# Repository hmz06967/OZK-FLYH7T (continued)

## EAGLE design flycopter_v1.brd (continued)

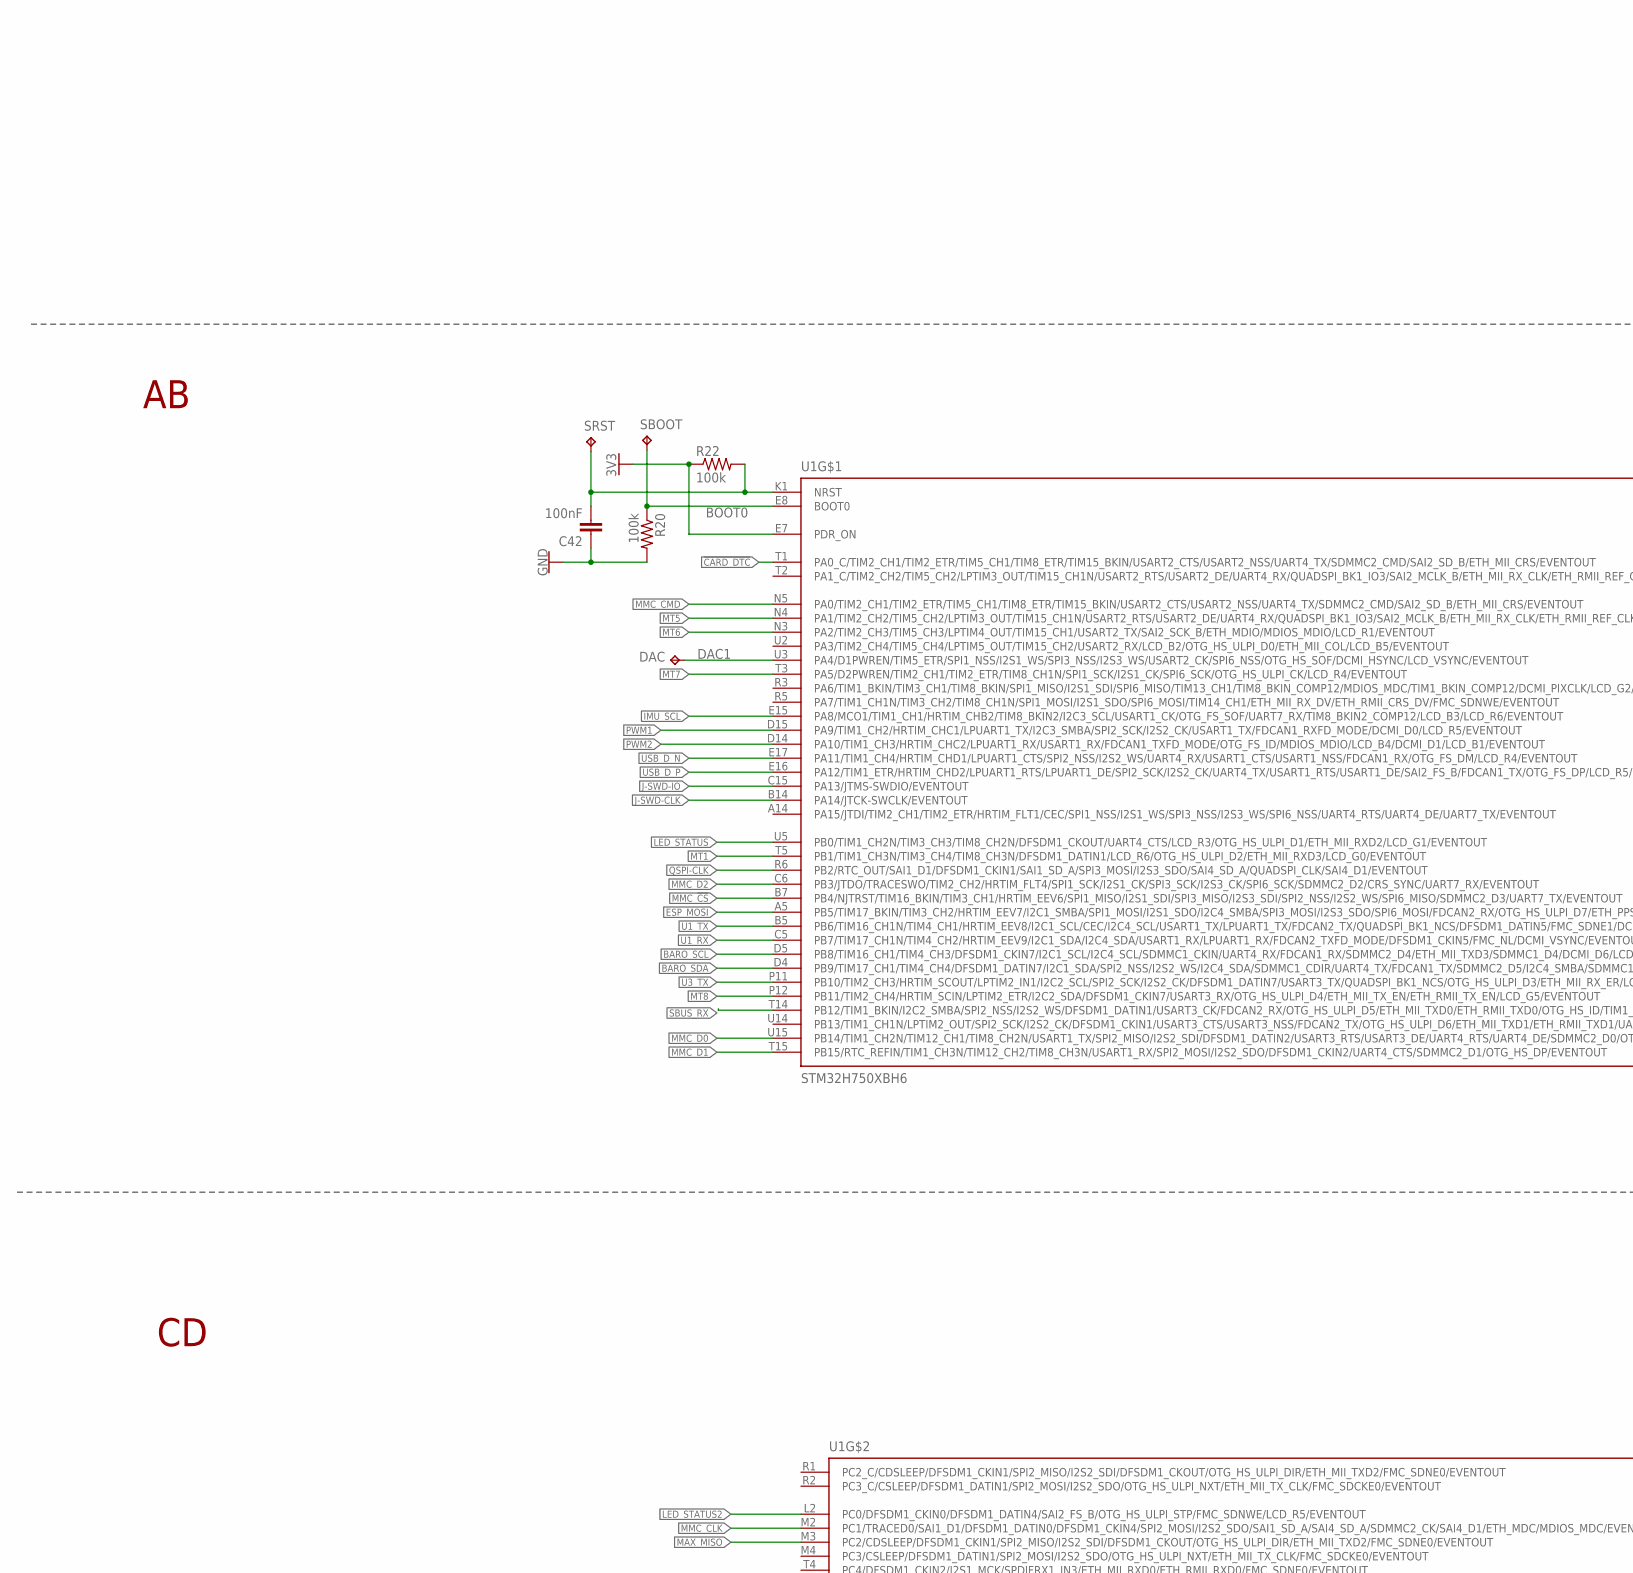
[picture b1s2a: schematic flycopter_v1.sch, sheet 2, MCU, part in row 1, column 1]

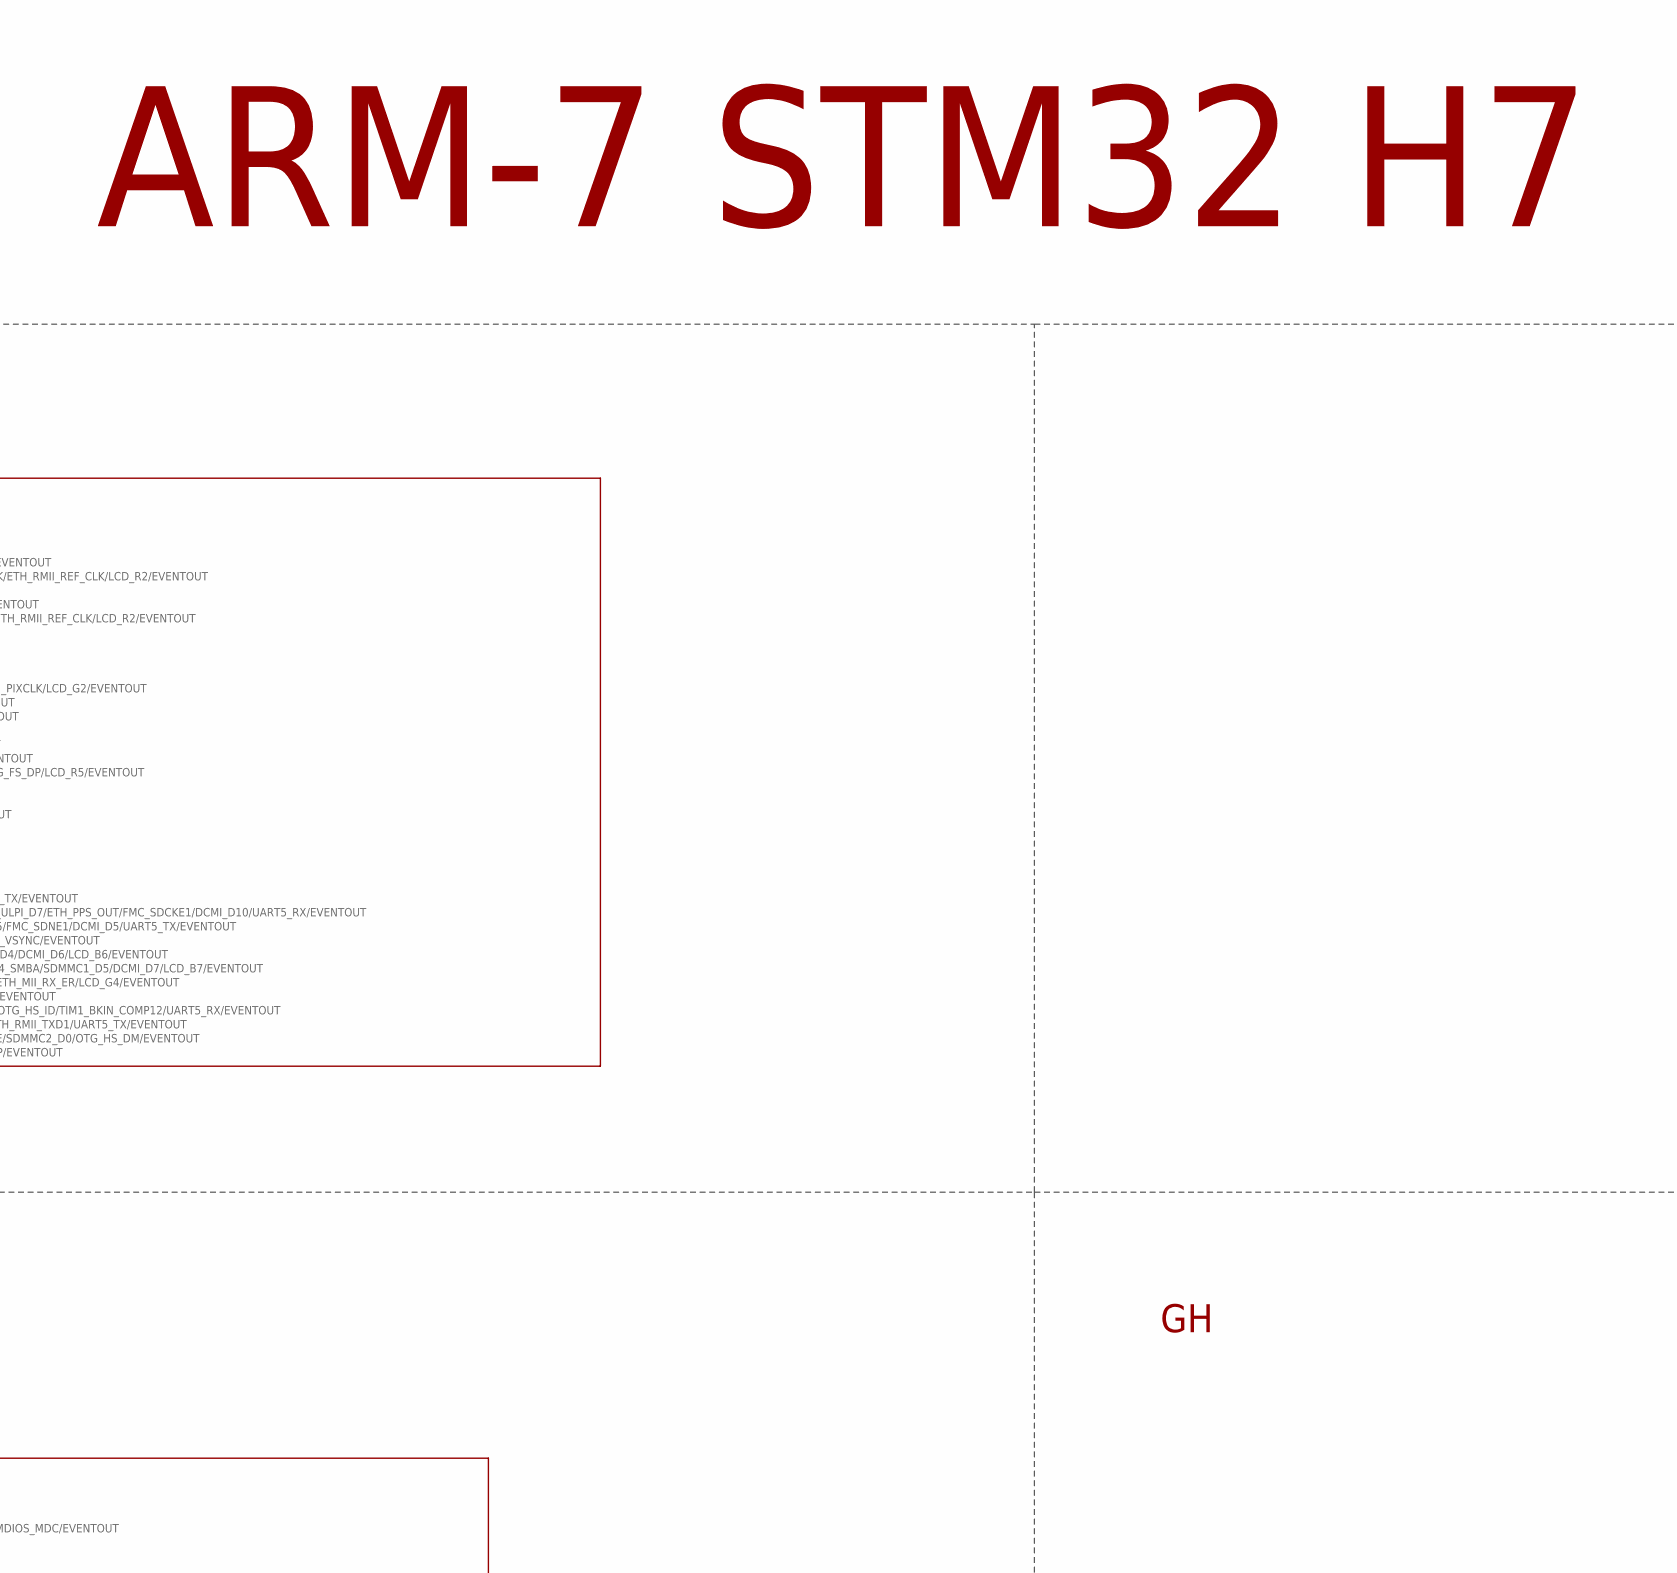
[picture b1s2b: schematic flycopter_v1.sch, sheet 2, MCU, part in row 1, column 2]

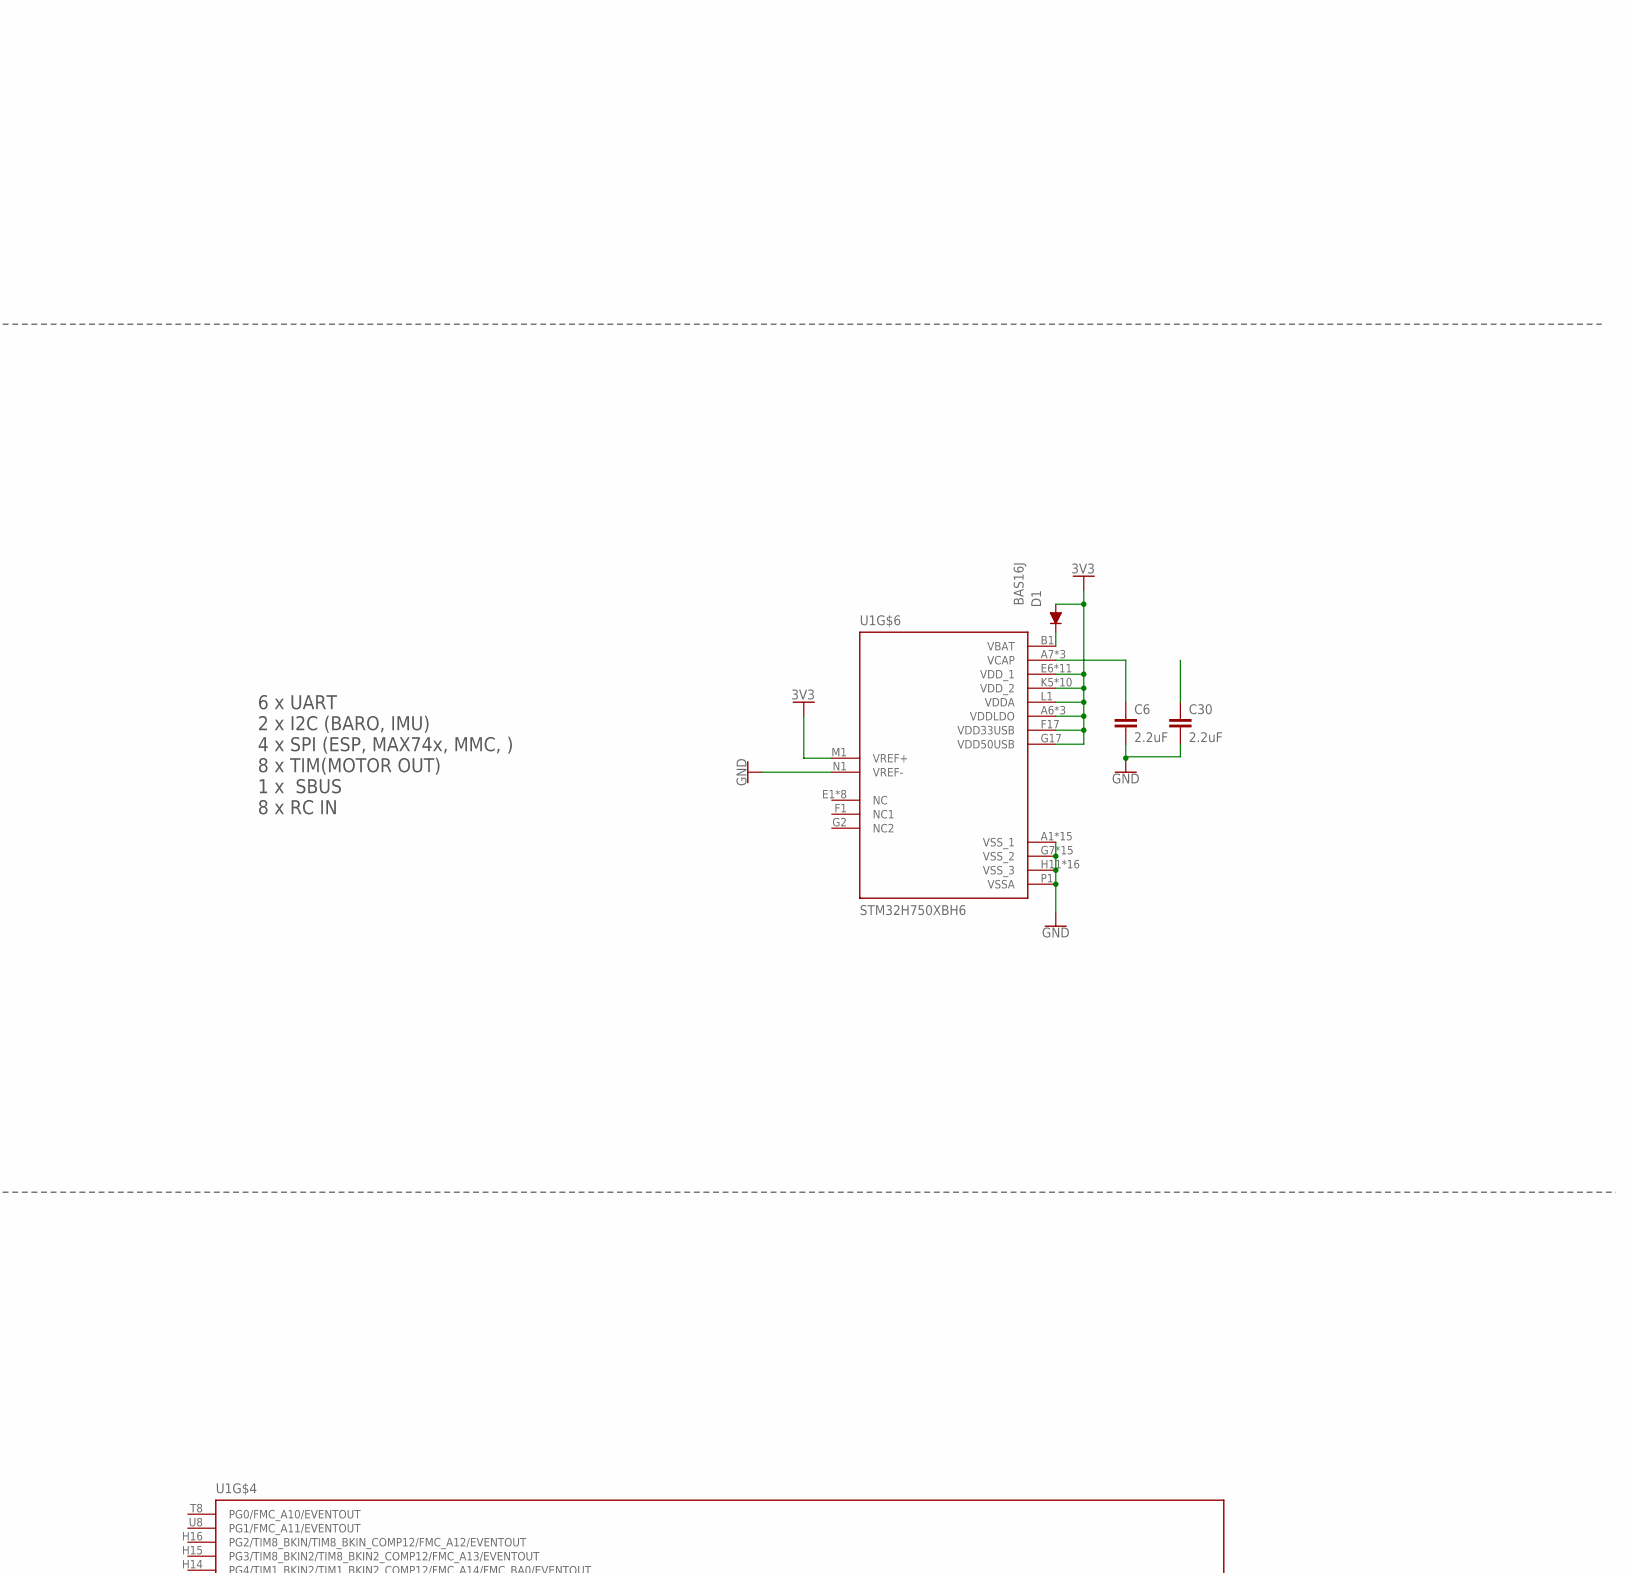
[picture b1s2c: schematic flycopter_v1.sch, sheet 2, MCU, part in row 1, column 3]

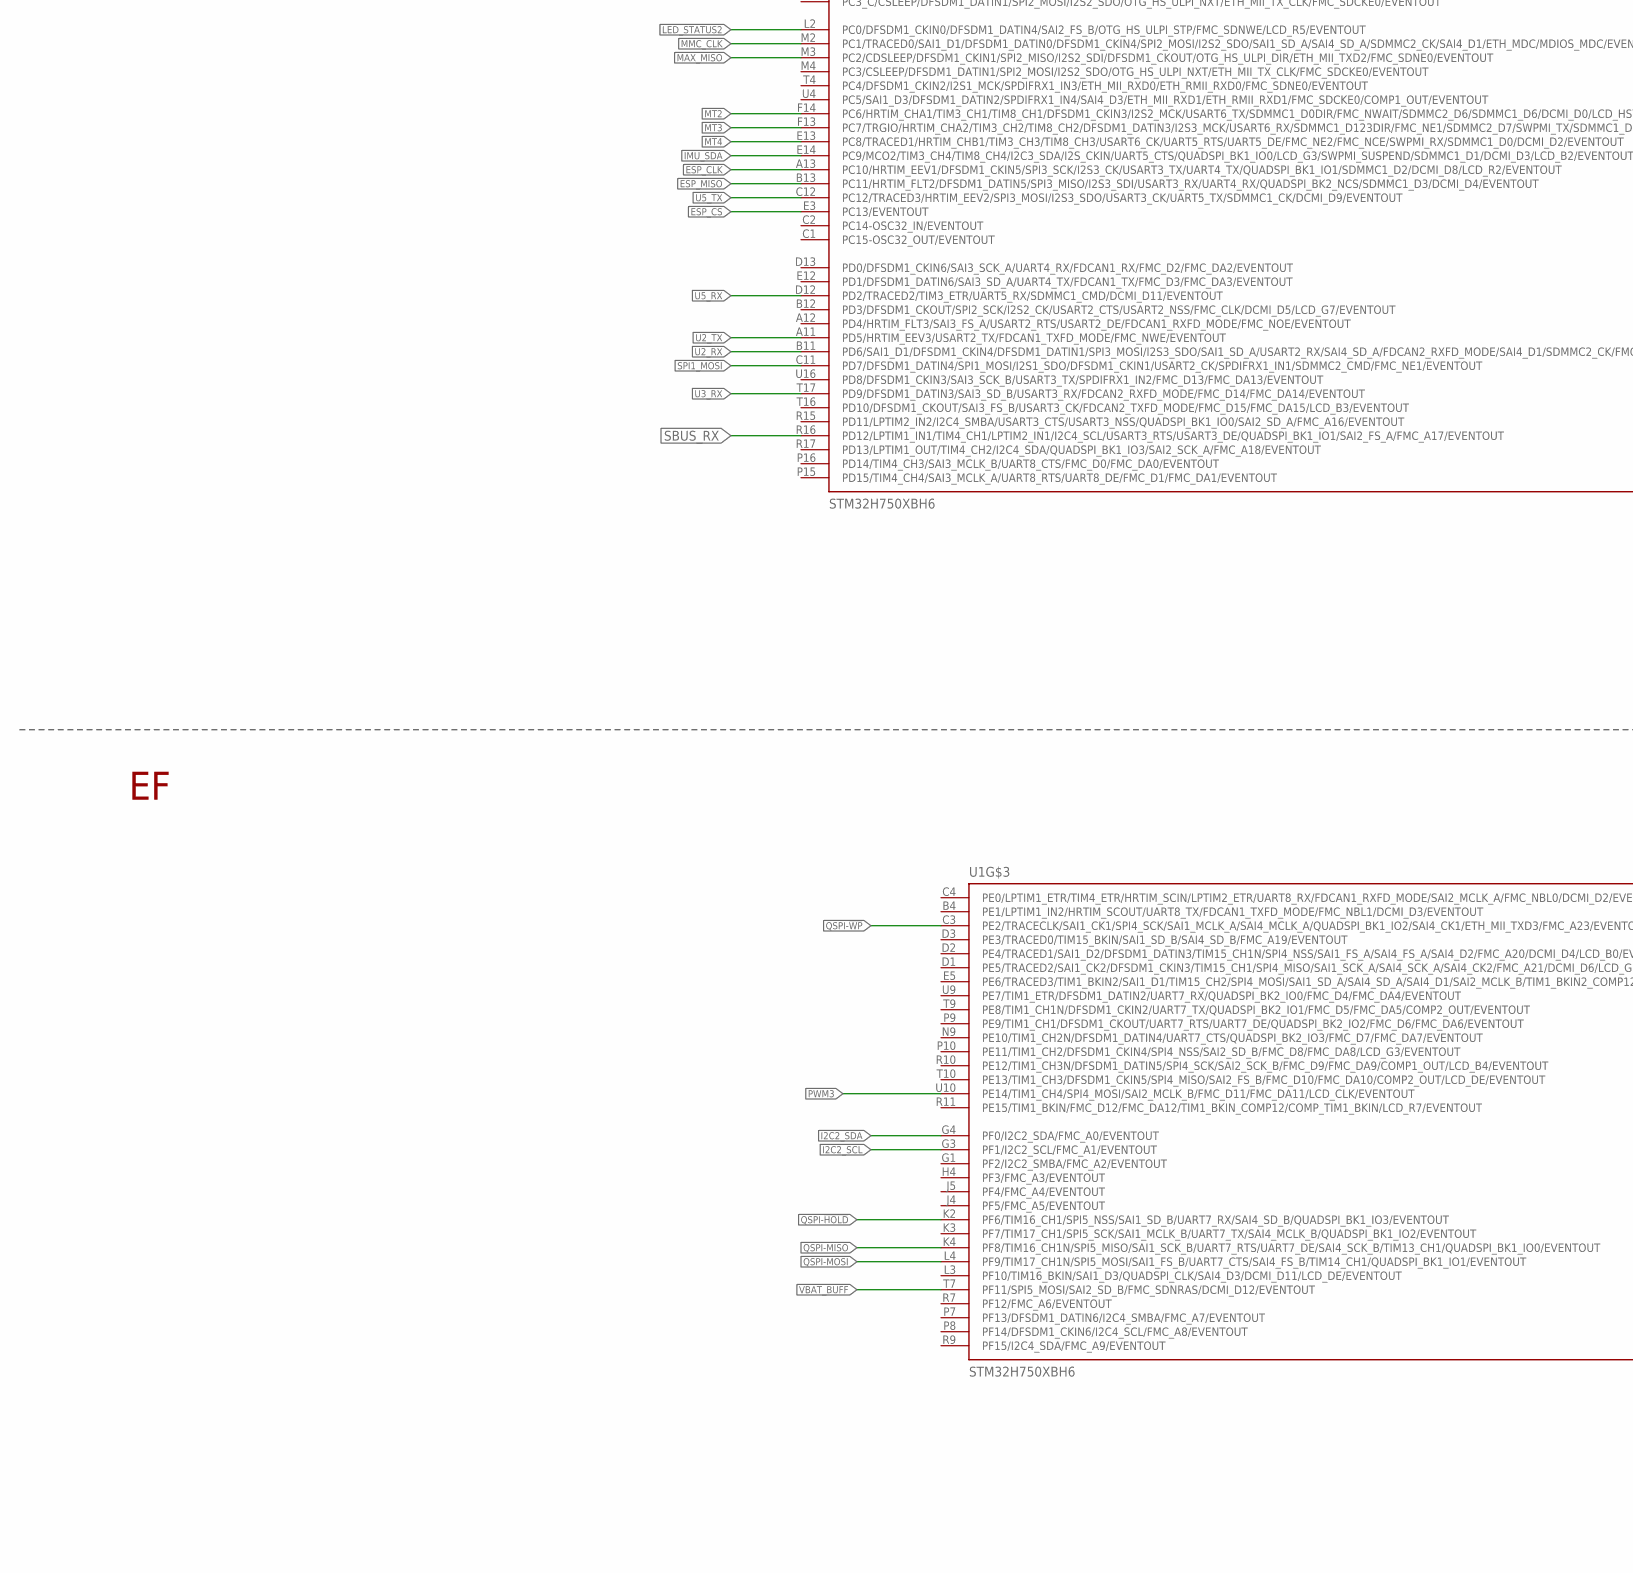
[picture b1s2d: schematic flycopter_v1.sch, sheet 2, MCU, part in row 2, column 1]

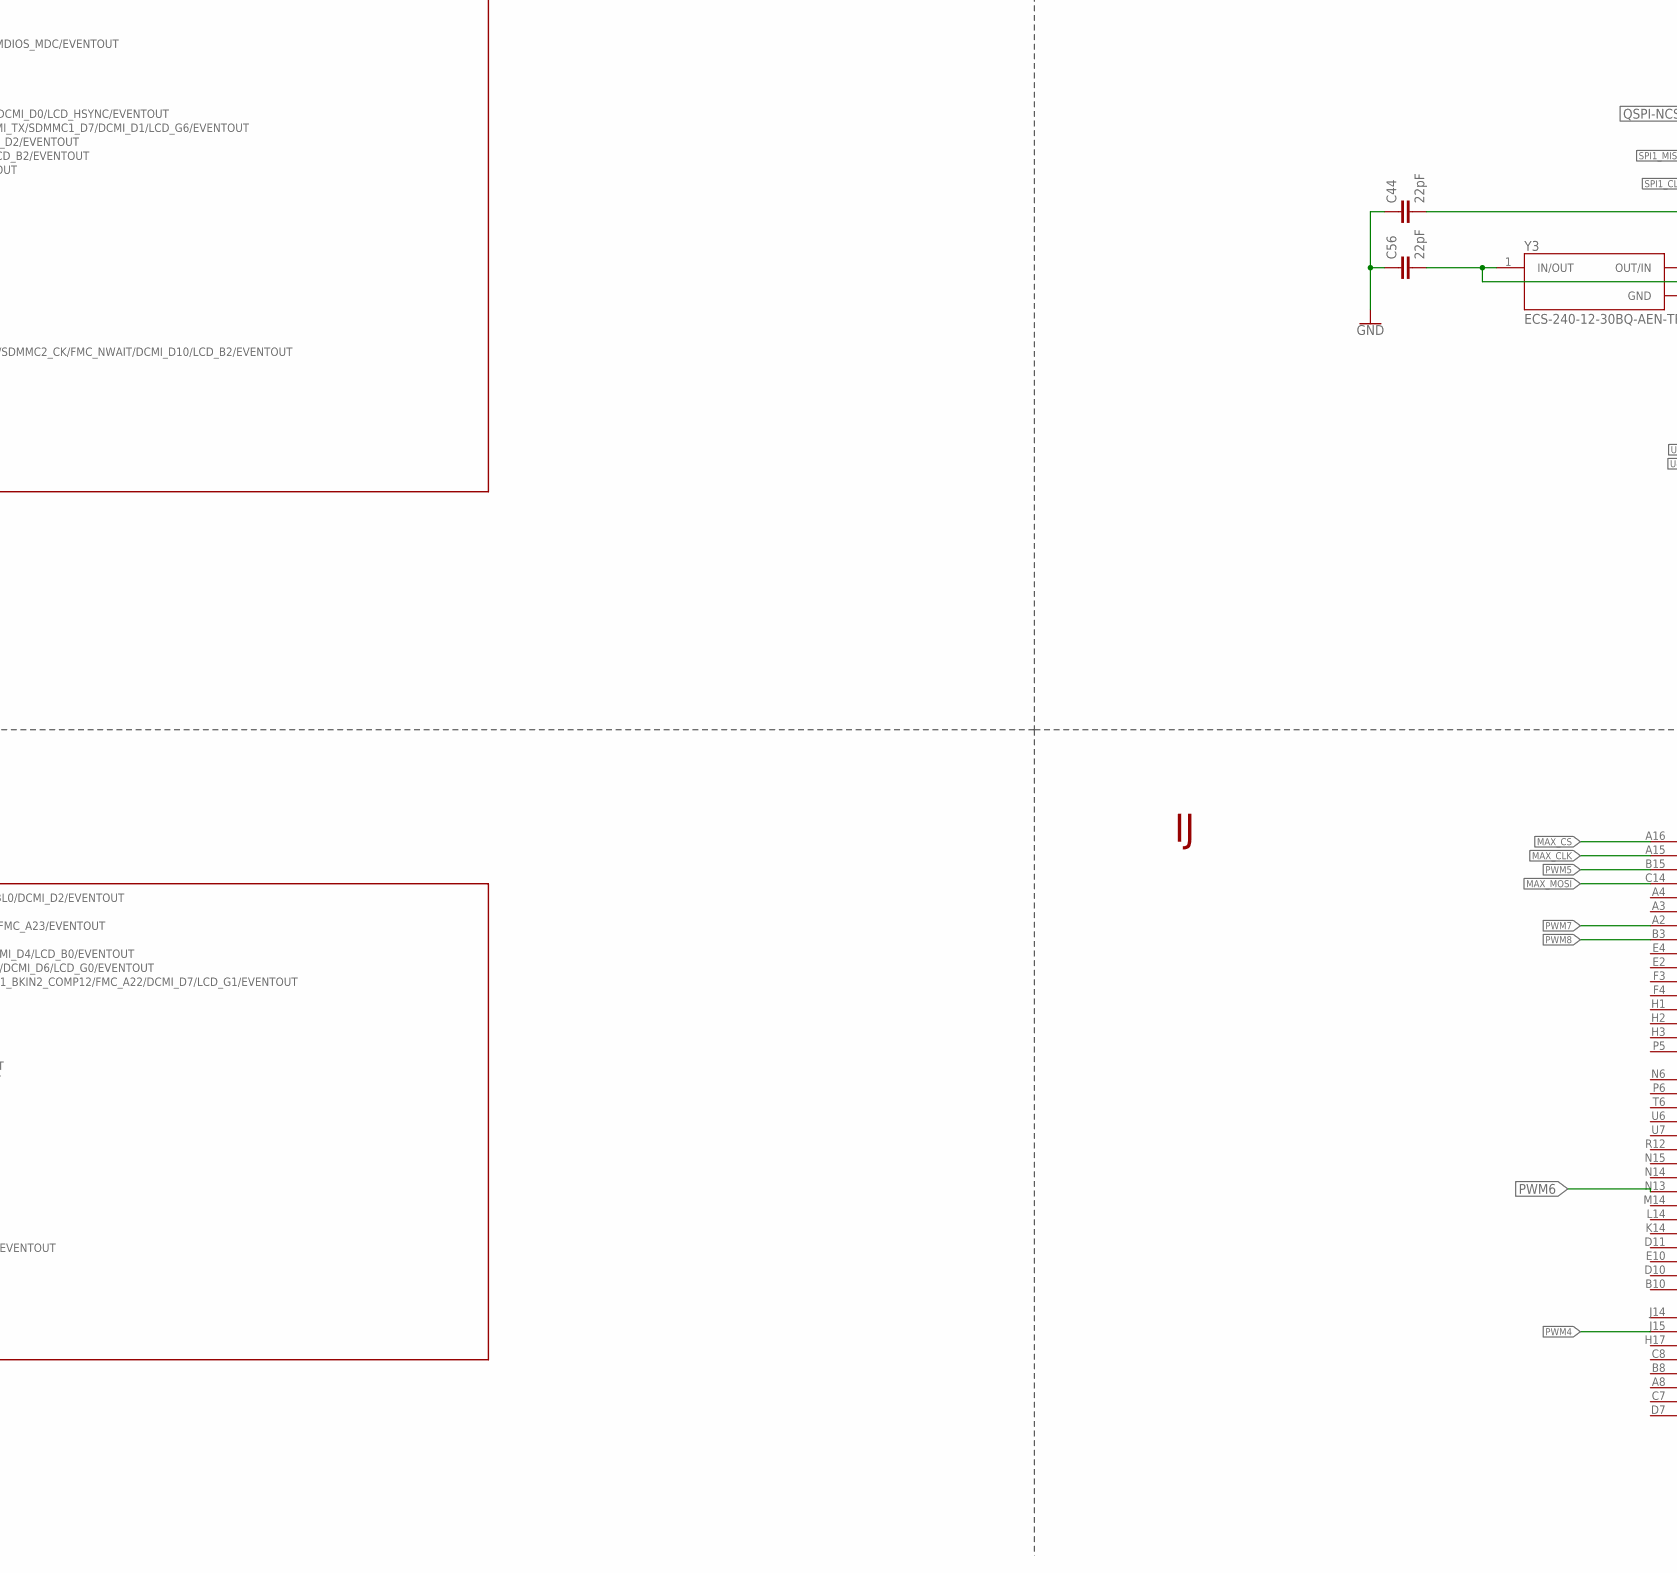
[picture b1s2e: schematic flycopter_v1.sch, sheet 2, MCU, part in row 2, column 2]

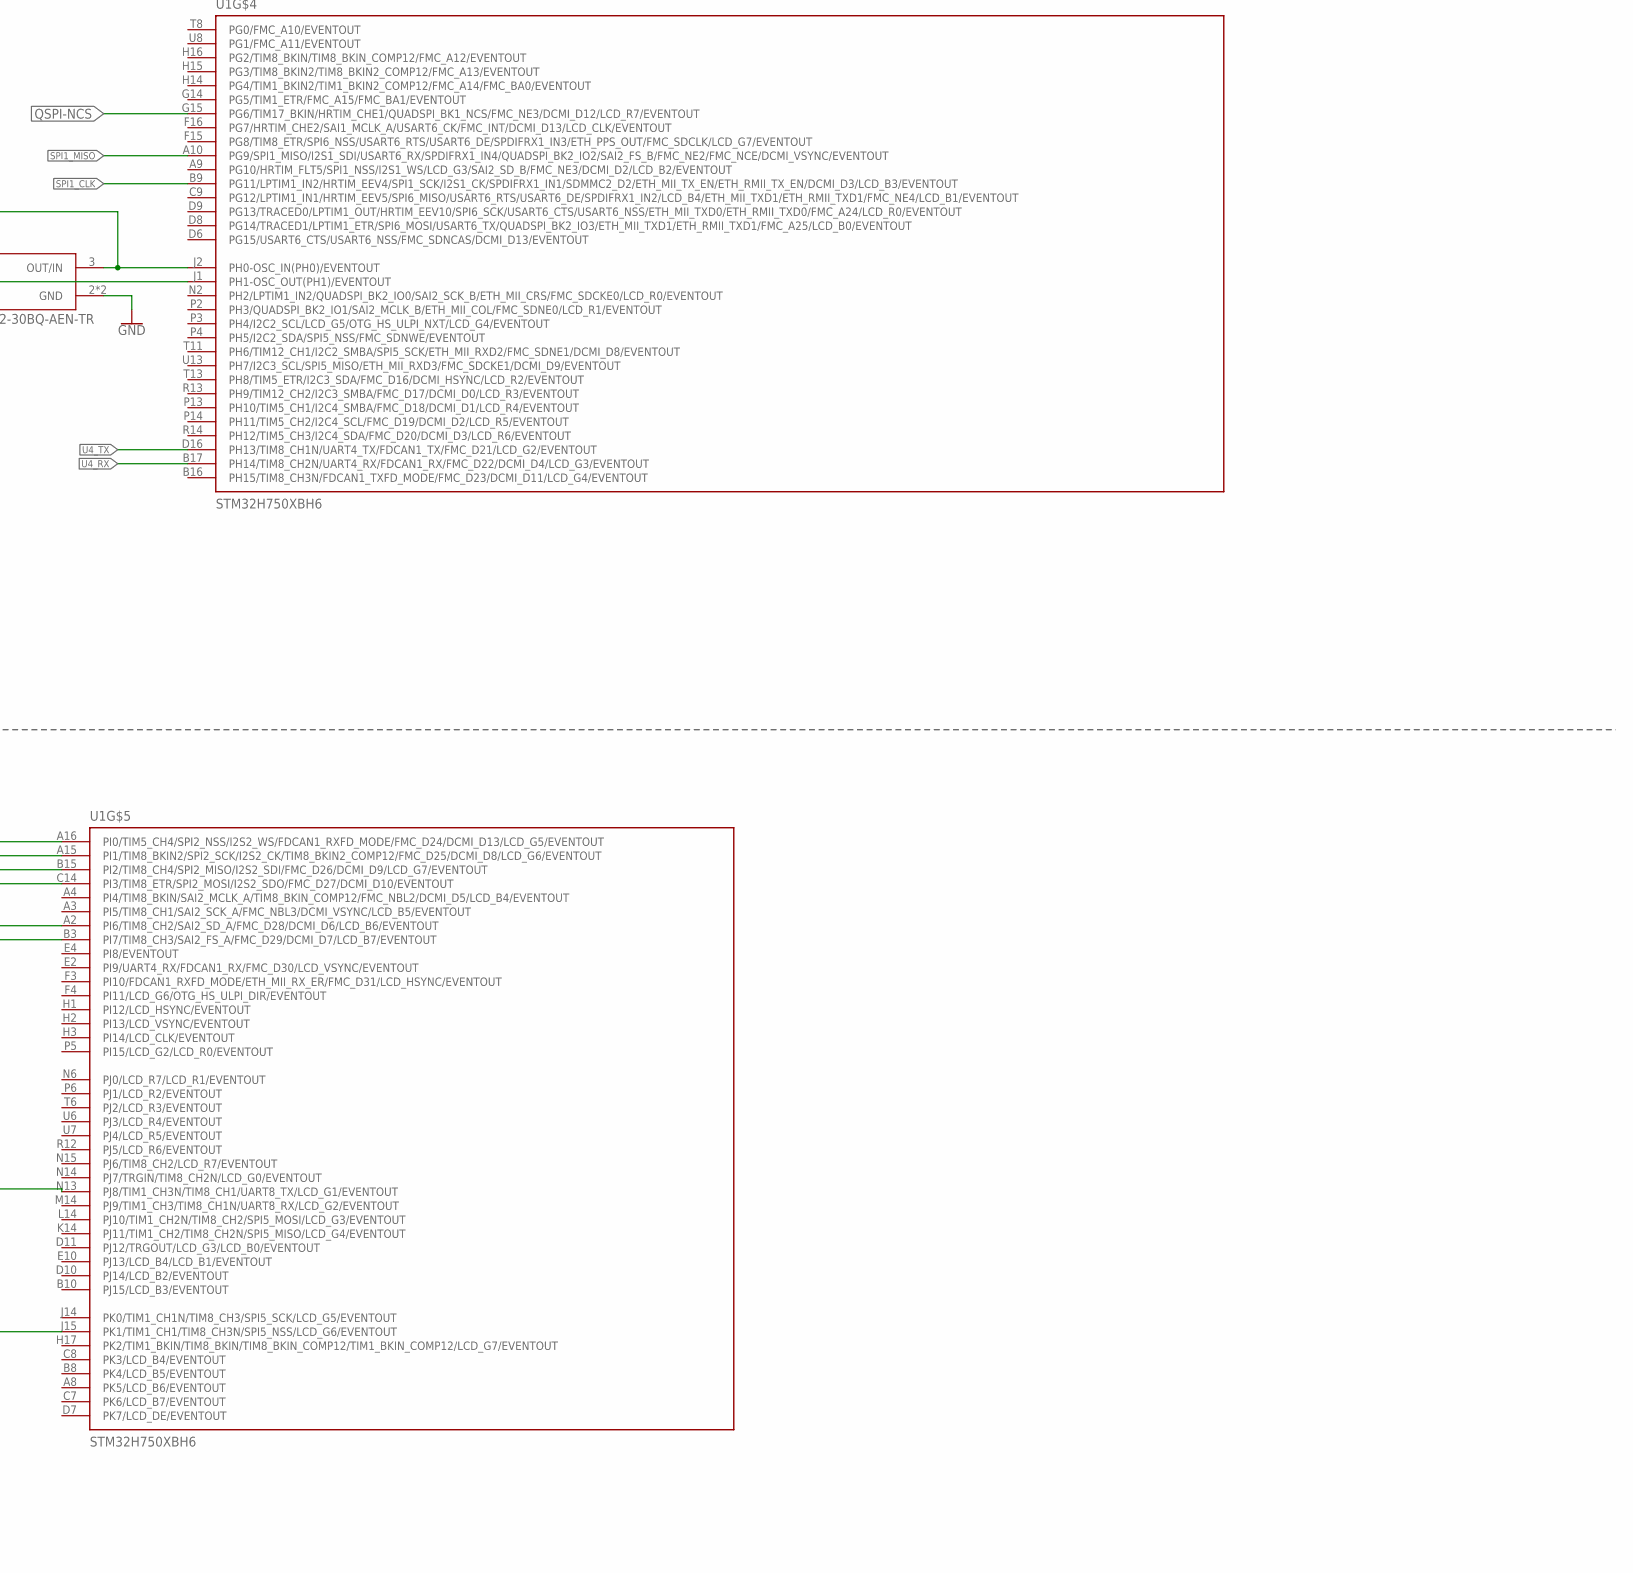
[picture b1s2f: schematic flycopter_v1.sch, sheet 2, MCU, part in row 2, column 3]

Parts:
C6, C30: 2.2uF; C0603K
C42: 100nF; C0603K
C44, C56: 22pF; C0402K
D1: BAS16J; DIODE_SOD123
DAC: TPTP06R; TP06R
R20, R22: 100k; R0402
SBOOT: TPTP06R; TP06R
SRST: TPTP06R; TP06R
U1: STM32H750XBH6; IC_STM32H750XBH6
Y3: ECS-240-12-30BQ-AEN-TR; XTAL_ECS-240-12-30BQ-AEN-TR

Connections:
3V3: D1.A, R22.1, U1.A6 (VDDLDO), U1.C17 (VDDLDO), U1.E6 (VDD_1), U1.E7 (PDR_ON), U1.E9 (VDD_1), U1.E11 (VDD_1), U1.F5 (VDD_1), U1.F17 (VDD33USB), U1.G5 (VDD_1), U1.G13 (VDD_1), U1.G17 (VDD50USB), U1.H5 (VDD_1), U1.H13 (VDD_1), U1.J13 (VDD_1), U1.K5 (VDD_2), U1.K13 (VDD_1), U1.L1 (VDDA), U1.L5 (VDD_2), U1.L13 (VDD_1), U1.M1 (VREF+), U1.M5 (VDD_2), U1.M13 (VDD_2), U1.N7 (VDD_2), U1.N8 (VDD_2), U1.N10 (VDD_2), U1.N11 (VDD_2), U1.N12 (VDD_2), U1.P17 (VDD_2), U1.U12 (VDDLDO); also elsewhere on the board
!CARD_DTC: U1.T1 (PA0_C/TIM2_CH1/TIM2_ETR/TIM5_CH1/TIM8_E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); also elsewhere on the board
BARO_SCL: U1.D5 (PB8/TIM16_CH1/TIM4_CH3/DFSDM1_CKIN7/I2C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); also elsewhere on the board
BARO_SDA: U1.D4 (PB9/TIM17_CH1/TIM4_CH4/DFSDM1_DATIN7/I2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); also elsewhere on the board
BOOT0: R20.1, SBOOT.TP, U1.E8 (BOOT0)
DAC1: DAC.TP, U1.U3 (PA4/D1PWREN/TIM5_ETR/SPI1_NSS/I2S1_WS/S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)
ESP_CLK: U1.A13 (PC10/HRTIM_EEV1/DFSDM1_CKIN5/SPI3_SCK/I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); also elsewhere on the board
ESP_CS: U1.E3 (PC13/EVENTOUT); also elsewhere on the board
ESP_MISO: U1.B13 (PC11/HRTIM_FLT2/DFSDM1_DATIN5/SPI3_MISO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); also elsewhere on the board
ESP_MOSI: U1.A5 (PB5/TIM17_BKIN/TIM3_CH2/HRTIM_EEV7/I2C1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); also elsewhere on the board
GND: C6.2, C30.2, C42.1, C44.1, C56.1, R20.2, U1.A1 (VSS_1), U1.A17 (VSS_1), U1.B2 (VSS_1), U1.B6 (VSS_1), U1.C10 (VSS_1), U1.C13 (VSS_1), U1.C16 (VSS_1), U1.F2 (VSS_1), U1.G7 (VSS_2), U1.G8 (VSS_2), U1.G9 (VSS_2), U1.G10 (VSS_2), U1.G11 (VSS_2), U1.G16 (VSS_2), U1.H7 (VSS_2), U1.H8 (VSS_2), U1.H9 (VSS_2), U1.H10 (VSS_2), U1.H11 (VSS_3), U1.J3 (VSS_1), U1.J7 (VSS_3), U1.J8 (VSS_3), U1.J9 (VSS_3), U1.J10 (VSS_3), U1.J11 (VSS_3), U1.J16 (VSS_1), U1.J17 (VSS_1), U1.K7 (VSS_3), U1.K8 (VSS_3), U1.K9 (VSS_3), U1.K10 (VSS_3), U1.K11 (VSS_3), U1.K15 (VSS_2), U1.L7 (VSS_3), U1.L8 (VSS_3), U1.L9 (VSS_3), U1.L10 (VSS_3), U1.L11 (VSS_3), U1.L15 (VSS_2), U1.M15 (VSS_2), U1.N1 (VREF-), U1.N16 (VSS_1), U1.P1 (VSSA), U1.R4 (VSS_1), U1.R8 (VSS_2), U1.T12 (VSS_1), U1.U1 (VSS_2), U1.U17 (VSS_1), Y3.2 (GND), Y3.4 (GND); also elsewhere on the board
I2C2_SCL: U1.G3 (PF1/I2C2_SCL/FMC_A1/EVENTOUT); also elsewhere on the board
I2C2_SDA: U1.G4 (PF0/I2C2_SDA/FMC_A0/EVENTOUT); also elsewhere on the board
IMU_SCL: U1.E15 (PA8/MCO1/TIM1_CH1/HRTIM_CHB2/TIM8_BKIN2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); also elsewhere on the board
IMU_SDA: U1.E14 (PC9/MCO2/TIM3_CH4/TIM8_CH4/I2C3_SDA/I2S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); also elsewhere on the board
J-SWD-CLK: U1.B14 (PA14/JTCK-SWCLK/EVENTOUT); also elsewhere on the board
J-SWD-IO: U1.C15 (PA13/JTMS-SWDIO/EVENTOUT); also elsewhere on the board
LED_STATUS: U1.U5 (PB0/TIM1_CH2N/TIM3_CH3/TIM8_CH2N/DFSDM1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); also elsewhere on the board
LED_STATUS2: U1.L2 (PC0/DFSDM1_CKIN0/DFSDM1_DATIN4/SAI2_FS_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); also elsewhere on the board
MAX_CLK: U1.A15 (PI1/TIM8_BKIN2/SPI2_SCK/I2S2_CK/TIM8_BK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); also elsewhere on the board
MAX_CS: U1.A16 (PI0/TIM5_CH4/SPI2_NSS/I2S2_WS/FDCAN1_RX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); also elsewhere on the board
MAX_MISO: U1.M3 (PC2/CDSLEEP/DFSDM1_CKIN1/SPI2_MISO/I2S2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); also elsewhere on the board
MAX_MOSI: U1.C14 (PI3/TIM8_ETR/SPI2_MOSI/I2S2_SDO/FMC_D27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); also elsewhere on the board
MMC_!CS: U1.B7 (PB4/NJTRST/TIM16_BKIN/TIM3_CH1/HRTIM_EE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); also elsewhere on the board
MMC_CLK: U1.M2 (PC1/TRACED0/SAI1_D1/DFSDM1_DATIN0/DFSDM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); also elsewhere on the board
MMC_CMD: U1.N5 (PA0/TIM2_CH1/TIM2_ETR/TIM5_CH1/TIM8_ETR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); also elsewhere on the board
MMC_D0: U1.U15 (PB14/TIM1_CH2N/TIM12_CH1/TIM8_CH2N/USAR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); also elsewhere on the board
MMC_D1: U1.T15 (PB15/RTC_REFIN/TIM1_CH3N/TIM12_CH2/TIM8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); also elsewhere on the board
MMC_D2: U1.C6 (PB3/JTDO/TRACESWO/TIM2_CH2/HRTIM_FLT4/S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); also elsewhere on the board
MT1: U1.T5 (PB1/TIM1_CH3N/TIM3_CH4/TIM8_CH3N/DFSDM1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); also elsewhere on the board
MT2: U1.F14 (PC6/HRTIM_CHA1/TIM3_CH1/TIM8_CH1/DFSDM1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); also elsewhere on the board
MT3: U1.F13 (PC7/TRGIO/HRTIM_CHA2/TIM3_CH2/TIM8_CH2/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); also elsewhere on the board
MT4: U1.E13 (PC8/TRACED1/HRTIM_CHB1/TIM3_CH3/TIM8_CH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); also elsewhere on the board
MT5: U1.N4 (PA1/TIM2_CH2/TIM5_CH2/LPTIM3_OUT/TIM15_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); also elsewhere on the board
MT6: U1.N3 (PA2/TIM2_CH3/TIM5_CH3/LPTIM4_OUT/TIM15_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); also elsewhere on the board
MT7: U1.T3 (PA5/D2PWREN/TIM2_CH1/TIM2_ETR/TIM8_CH1N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); also elsewhere on the board
MT8: U1.P12 (PB11/TIM2_CH4/HRTIM_SCIN/LPTIM2_ETR/I2C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); also elsewhere on the board
unnamed: C42.2, R22.2, SRST.TP, U1.K1 (NRST)
unnamed: D1.C, U1.B1 (VBAT)
unnamed: C6.1, U1.A7 (VCAP), U1.D17 (VCAP), U1.U11 (VCAP)
unnamed: C44.2, U1.J2 (PH0-OSC_IN(PH0)/EVENTOUT), Y3.3 (OUT/IN)
unnamed: C56.2, U1.J1 (PH1-OSC_OUT(PH1)/EVENTOUT), Y3.1 (IN/OUT)
PWM1: U1.D15 (PA9/TIM1_CH2/HRTIM_CHC1/LPUART1_TX/I2C3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); also elsewhere on the board
PWM2: U1.D14 (PA10/TIM1_CH3/HRTIM_CHC2/LPUART1_RX/USA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); also elsewhere on the board
PWM3: U1.U10 (PE14/TIM1_CH4/SPI4_MOSI/SAI2_MCLK_B/FMC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); also elsewhere on the board
PWM4: U1.J15 (PK1/TIM1_CH1/TIM8_CH3N/SPI5_NSS/LCD_G6/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); also elsewhere on the board
PWM5: U1.B15 (PI2/TIM8_CH4/SPI2_MISO/I2S2_SDI/FMC_D26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); also elsewhere on the board
PWM6: U1.N13 (PJ8/TIM1_CH3N/TIM8_CH1/UART8_TX/LCD_G1/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); also elsewhere on the board
PWM7: U1.A2 (PI6/TIM8_CH2/SAI2_SD_A/FMC_D28/DCMI_D6/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); also elsewhere on the board
PWM8: U1.B3 (PI7/TIM8_CH3/SAI2_FS_A/FMC_D29/DCMI_D7/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); also elsewhere on the board
QSPI-!HOLD: U1.K2 (PF6/TIM16_CH1/SPI5_NSS/SAI1_SD_B/UART7_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); also elsewhere on the board
QSPI-!WP: U1.C3 (PE2/TRACECLK/SAI1_CK1/SPI4_SCK/SAI1_MCL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); also elsewhere on the board
QSPI-CLK: U1.R6 (PB2/RTC_OUT/SAI1_D1/DFSDM1_CKIN1/SAI1_S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); also elsewhere on the board
QSPI-MISO: U1.K4 (PF8/TIM16_CH1N/SPI5_MISO/SAI1_SCK_B/UAR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); also elsewhere on the board
QSPI-MOSI: U1.L4 (PF9/TIM17_CH1N/SPI5_MOSI/SAI1_FS_B/UART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); also elsewhere on the board
QSPI-NCS: U1.G15 (PG6/TIM17_BKIN/HRTIM_CHE1/QUADSPI_BK1_N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); also elsewhere on the board
SBUS_RX: U1.R16 (PD12/LPTIM1_IN1/TIM4_CH1/LPTIM2_IN1/I2C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), U1.T14 (PB12/TIM1_BKIN/I2C2_SMBA/SPI2_NSS/I2S2_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); also elsewhere on the board
SPI1_CLK: U1.B9 (PG11/LPTIM1_IN2/HRTIM_EEV4/SPI1_SCK/I2S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)
SPI1_MISO: U1.A10 (PG9/SPI1_MISO/I2S1_SDI/USART6_RX/SPDIFR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)
SPI1_MOSI: U1.C11 (PD7/DFSDM1_DATIN4/SPI1_MOSI/I2S1_SDO/DF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)
U1_RX: U1.C5 (PB7/TIM17_CH1N/TIM4_CH2/HRTIM_EEV9/I2C1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); also elsewhere on the board
U1_TX: U1.B5 (PB6/TIM16_CH1N/TIM4_CH1/HRTIM_EEV8/I2C1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); also elsewhere on the board
U2_RX: U1.B11 (PD6/SAI1_D1/DFSDM1_CKIN4/DFSDM1_DATIN1/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)
U2_TX: U1.A11 (PD5/HRTIM_EEV3/USART2_TX/FDCAN1_TXFD_MO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)
U3_RX: U1.T17 (PD9/DFSDM1_DATIN3/SAI3_SD_B/USART3_RX/F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); also elsewhere on the board
U3_TX: U1.P11 (PB10/TIM2_CH3/HRTIM_SCOUT/LPTIM2_IN1/I2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); also elsewhere on the board
U4_RX: U1.B17 (PH14/TIM8_CH2N/UART4_RX/FDCAN1_RX/FMC_D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); also elsewhere on the board
U4_TX: U1.D16 (PH13/TIM8_CH1N/UART4_TX/FDCAN1_TX/FMC_D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); also elsewhere on the board
U5_RX: U1.D12 (PD2/TRACED2/TIM3_ETR/UART5_RX/SDMMC1_CM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); also elsewhere on the board
U5_TX: U1.C12 (PC12/TRACED3/HRTIM_EEV2/SPI3_MOSI/I2S3_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); also elsewhere on the board
USB_D_N: U1.E17 (PA11/TIM1_CH4/HRTIM_CHD1/LPUART1_CTS/SP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); also elsewhere on the board
USB_D_P: U1.E16 (PA12/TIM1_ETR/HRTIM_CHD2/LPUART1_RTS/LP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); also elsewhere on the board
VBAT_BUFF: U1.T7 (PF11/SPI5_MOSI/SAI2_SD_B/FMC_SDNRAS/DCM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); also elsewhere on the board

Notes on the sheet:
6 x UART 2 x I2C (BARO, IMU) 4 x SPI (ESP, MAX74x, MMC, ) 8 x TIM(MOTOR OUT) 1 x SBUS 8 x RC IN
ARM-7 STM32 H7
